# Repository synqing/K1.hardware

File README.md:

# K1.hardware

Agent-driven KiCad and PCB automation for K1-Lightwave hardware.

This repository contains public tooling, MCP servers, reference material, and prototype automation used around the K1-Lightwave hardware workflow. Product PCB files, fabrication outputs, BOMs, and private design documents are not published in the public HEAD of this repository.

> [!NOTE]
> This public surface is being cleaned up for transfer into the SpectraSynq organisation. Some legacy prototype tooling is preserved for reference, but it should not be treated as a stable package API until it is extracted into a dedicated tool repository.

## Quickstart

```bash
git clone https://github.com/synqing/K1.hardware.git
cd K1.hardware
python3 mcp/verify-servers.py
python3 mcp/test_rag.py
```

For Claude Code MCP setup, run:

```bash
python3 mcp/configure_claude.py
```

Some integrations need your own API credentials. See [SETUP_CREDENTIALS.md](docs/internal/legacy-root/SETUP_CREDENTIALS.md) for provider setup notes.

## What is here

- **MCP servers** in [mcp/](mcp/) for KiCad CLI automation, KiKit, KiBot, SKiDL, FreeRouting, component sourcing, fab operations, and local RAG.
- **Agent modules** in [agent/](agent/) for DFM checks, KiCad helpers, routing, impedance, thermal modelling, and orchestration.
- **Tool prototypes** in [tools/](tools/), including the KiCad footprint hunter and the preserved Elite PCB Designer prototype.
- **Reference docs** in [docs/](docs/) for public tooling notes, vendor references, datasheets, and legacy implementation notes.

## Repository layout

```text
K1.hardware/
|-- agent/                         Python modules for PCB automation workflows
|-- docs/                          Public references and legacy notes
|-- mcp/                           MCP servers used by agent-driven EDA workflows
|-- plugins/                       KiCad plugin experiments
|-- tools/
|   |-- elite-pcb-designer/        Prototype routing, placement, and validation tooling
|   `-- kicad-footprint-hunter/    Footprint discovery and board update utilities
|-- .github/                       Workflow definitions retained for review
|-- .gitignore
|-- LICENSE
`-- README.md
```

## Working with the tools

Use [mcp/verify-servers.py](mcp/verify-servers.py) to check local dependencies and MCP server availability. Use [mcp/test_rag.py](mcp/test_rag.py) to confirm the local RAG index can answer tooling queries.

The legacy Elite PCB Designer prototype now lives under [tools/elite-pcb-designer/legacy-pipeline/](tools/elite-pcb-designer/legacy-pipeline/). Run those scripts from that directory, and expect to provide your own KiCad input files.

## Community and support

- [Issues](../../issues) for bugs, cleanup findings, and extraction candidates.
- [Discord](https://discord.gg/8y8rXegU8j) for SpectraSynq build discussion.

## Licence

Code is licensed under Apache-2.0; see [LICENSE](LICENSE). Documentation is licensed under [CC BY 4.0](https://creativecommons.org/licenses/by/4.0/) unless a source document states otherwise.

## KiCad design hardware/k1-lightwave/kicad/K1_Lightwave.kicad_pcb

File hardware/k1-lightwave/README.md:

# K1 Lightwave Hardware Design — Tooling Guide

This folder contains the KiCad schematic, PCB layout, and supporting design files for the K1 Lightwave dual-ESP32-S3 music visualizer.

---

## Folder Structure

```
k1-lightwave/
├── kicad/
│   ├── K1_Lightwave.kicad_sch      ← Master schematic
│   ├── K1_Lightwave.kicad_pcb      ← PCB layout
│   ├── K1_Lightwave.kicad_pro      ← KiCad project file
│   ├── symbols/                    ← Custom/library symbols
│   ├── footprints/                 ← Custom/library footprints
│   └── 3d_models/                  ← 3D STEP/VRML models
├── skidl/
│   └── hello_board.py              ← Example SKiDL schematic generator
└── README.md                         ← You are here
```

---

## MCP Tool Commands

All tools are wired as Claude Code MCP servers. Use them to validate design changes.

### **Electrical Rules Check (ERC)**

```
sch_erc(schematic, out="erc.json", format="json", exit_code_violations=True)
```

**Example:**
```python
result = sch_erc("hardware/k1-lightwave/kicad/K1_Lightwave.kicad_sch", out="erc.json")
# Returns: {"returncode": 0, "ok": true, "summary": {"errors": 0, "warnings": 0}}
```

**Pass criteria:** `error_count == 0`

---

### **Design Rules Check (DRC)**

```
pcb_drc(board, out="drc.json", format="json", exit_code_violations=True)
```

**Example:**
```python
result = pcb_drc("hardware/k1-lightwave/kicad/K1_Lightwave.kicad_pcb", out="drc.json")
# Returns: {"returncode": 0, "ok": true, "summary": {"violations": 0}}
```

**Pass criteria:** `violations == 0` (JLC 4-layer rules in `design_rules.kicad_dru`)

---

### **Bill of Materials (BOM) Export**

```
sch_export_bom(schematic, out_csv="bom.csv", fields="*")
```

**Example:**
```python
result = sch_export_bom("hardware/k1-lightwave/kicad/K1_Lightwave.kicad_sch", out_csv="bom.csv")
# Exports: bom.csv with all component fields
```

---

### **Netlist Export** (for routing/SKiDL)

```
sch_export_netlist(schematic, out_net="project.net", fmt="kicadsexpr")
```

**Example:**
```python
result = sch_export_netlist("hardware/k1-lightwave/kicad/K1_Lightwave.kicad_sch", out_net="k1.net")
# Exports: S-expression netlist for DSN → routing workflow
```

---

### **Gerber/Drill/STEP/IPC-2581 Exports**

```
pcb_export_gerbers(board, out_dir="fab/gerbers")
pcb_export_drill(board, out_dir="fab/drill")
pcb_export_step(board, out_file="mechanical/board.step")
pcb_export_ipc2581(board, out_file="fab/board.ipc")
```

**Example:**
```python
pcb_export_gerbers("hardware/k1-lightwave/kicad/K1_Lightwave.kicad_pcb", out_dir="fab/gerbers")
pcb_export_drill("hardware/k1-lightwave/kicad/K1_Lightwave.kicad_pcb", out_dir="fab/drill")
pcb_export_step("hardware/k1-lightwave/kicad/K1_Lightwave.kicad_pcb", out_file="fab/board.step")
# Creates fab-ready artifacts
```

---

### **Netlist Generation from SKiDL**

```
skidl_gen_netlist(script_path="skidl/hello_board.py", out_net="skidl_out.net")
```

**Example:**
```python
result = skidl_gen_netlist("hardware/k1-lightwave/skidl/hello_board.py", out_net="k1.net")
# Returns: {"parts": 12, "nets": 8, "output": "/path/to/k1.net"}
```

---

### **Component Lookup (Nexar/LCSC)**

```
parts_search(q="ESP32-S3-WROOM-1", limit=3)
best_datasheet_url(mpn="WS2812B")
lcsc_search(keyword="C2653")
```

**Example:**
```python
result = parts_search("ESP32-S3-WROOM-1", limit=3)
# Returns: MPN, manufacturer, best_datasheet URL

ds = best_datasheet_url("WS2812B")
# Returns: {"mpn": "WS2812B", "url": "https://...", "ok": true}

item = lcsc_search("C2653")
# Returns: LCSC product info (pricing, stock, etc.)
```

---

### **Panelization (KiKit)**

```
kikit_panelize_grid(input_pcb, output_pcb, rows=4, cols=8, space_mm="2mm", tabs="full", cuts="vcuts; clearance: 0.4mm", rails_mm="5mm")
```

**Example:**
```python
result = kikit_panelize_grid(
    "hardware/k1-lightwave/kicad/K1_Lightwave.kicad_pcb",
    "hardware/k1-lightwave/kicad/K1_Lightwave_PANEL_4x8.kicad_pcb",
    rows=4, cols=8, space_mm="2mm", rails_mm="5mm"
)
# Creates panelized board with V-cuts and mousebites
```

---

### **JLC Assembly Pack (KiKit)**

```
kikit_fab_jlcpcb(board_or_panel, out_dir="fab/jlc", assembly=True, schematic="...", field="LCSC", autoname=True)
```

**Example:**
```python
result = kikit_fab_jlcpcb(
    "hardware/k1-lightwave/kicad/K1_Lightwave.kicad_pcb",
    out_dir="fab/jlc",
    assembly=True,
    schematic="hardware/k1-lightwave/kicad/K1_Lightwave.kicad_sch",
    field="LCSC"
)
# Generates: gerbers.zip, bom.csv, pos.csv (JLC-ready)
```

---

### **Interactive BOM (iBOM)**

```
generate(board_kicad_pcb, out_dir="docs/ibom", name_format="ibom", extra_fields="LCSC,MPN,Manufacturer")
```

**Example:**
```python
result = generate("hardware/k1-lightwave/kicad/K1_Lightwave.kicad_pcb", out_dir="docs/ibom")
# Creates: docs/ibom/ibom.html (self-contained assembly guide)
```

---

### **CI Automation (KiBot)**

```
kibot_run(project_dir="hardware/k1-lightwave", config_yaml="kibot.yaml", out_dir="_artifacts", schematic="...", board="...")
```

**Example:**
```python
result = kibot_run(
    project_dir="hardware/k1-lightwave",
    config_yaml="kibot.yaml",
    out_dir="_artifacts",
    schematic="kicad/K1_Lightwave.kicad_sch",
    board="kicad/K1_Lightwave.kicad_pcb"
)
# Runs full KiBot pipeline (ERC, DRC, exports, docs)
```

---

### **Autorouting (FreeRouting)**

```
route(dsn="export.dsn", ses_out="routed.ses", ignore_nets="", timeout_sec=300)
```

**Example:**
```python
result = route("kicad/K1_Lightwave.dsn", ses_out="kicad/K1_Lightwave.ses")
# Routes board from KiCad DSN export → SES session file
```

---

## ⚠️ Critical Safety: Dual 5V Rails

> **External LED 5V required.** USB-C 5V powers the controller only. Do not power LED strips from USB-C.
> Use the **LED_5V_IN** connector, one polyfuse per LED output, and keep LED return paths short.
>
> **Power-domain guard enabled:** Schematic-level check prevents shorts between `VBUS_USB_5V` and `LED_5V` nets.
> If any component accidentally ties both nets, the fab pipeline will reject the design.

---

## Design Rules & Constraints

### **Manufacturing (JLC PCBWay 4-layer)**

- **Minimum trace width:** 0.1mm
- **Minimum clearance:** 0.1mm
- **Via diameter (finished):** 0.3mm min
- **Stackup:** Signal / Plane / Plane / Signal
- **Impedance (controlled):** 50Ω differential for high-speed signals

### **Electrical (K1 Lightwave)**

- **VCC (3.3V logic):** ±0.1V regulation
- **Power (5V input):** 5A budget, adjust per LED load
- **USB 5V (controller):** Powers MCUs + audio codec only via LDO
- **LED 5V (external):** Separate connector; never tied to USB rail
- **I2S audio:** BCLK/LRCLK/SD differential, <0.5mm lengths matched
- **SPI (LED data):** <5mm tracklength to level shifter + MCU
- **Ground:** Multi-point return (polygon fill on both internal planes)

### **Thermal**

- **LED driver max dissipation:** 1.5W (estimate via chain coverage)
- **MCU under full load:** Monitor thermal rise via STEP export
- **Thermal vias under high-current:** 8–16× 0.3mm vias per component

### **Layout Best Practices**

- **RF keepout:** 5mm from ESP32 module antenna edge
- **Audio coupling:** Ground guard on I2S traces; min 0.5mm clearance from LED switching
- **Power distribution:** Use star grounding; separate analog/digital returns only if needed
- **Test points:** Add TP for each major rail + UART + LED data/clock

---

## Validation Checklist

Before committing design changes, run:

```bash
# 1. ERC
sch_erc("kicad/K1_Lightwave.kicad_sch", out="erc.json")
# Expected: error_count == 0

# 2. DRC
pcb_drc("kicad/K1_Lightwave.kicad_pcb", out="drc.json")
# Expected: violations == 0

# 3. BOM & component availability
sch_export_bom("kicad/K1_Lightwave.kicad_sch", out_csv="bom.csv")
parts_search("ESP32-S3-WROOM-1", limit=3)  # verify stock
best_datasheet_url("SPH0645")  # verify datasheets available

# 4. Mechanical (3D check)
pcb_export_step("kicad/K1_Lightwave.kicad_pcb", out_file="fab/board.step")
# View in 3D viewer to catch clearance issues

# 5. Manufacturing data
pcb_export_ipc2581("kicad/K1_Lightwave.kicad_pcb", out_file="fab/board.ipc")
# For DFM analysis at fab
```

---

## Documentation

- **Hardware PRD:** `/docs/prd/02-hardware-prd.md`
- **Validation Plan:** `/docs/prd/03-validation-plan.md`
- **Datasheets:** `/docs/datasheets/` (ESP32-S3, SPH0645, IM69D130, WS2812B, SN74AHCT125, etc.)
- **Governance:** `/claude/GOVERNANCE.md` (design change protocol)

---

## References

- **KiCad CLI:** https://docs.kicad.org/cli/
- **KiCad Project:** K1_Lightwave.kicad_pro (PCBNew, Schematic Editor)
- **JLC/PCBWay DRC:** `/docs/datasheets/jlc-pcbway-4layer-drc.pdf`
- **ESP32-S3 Datasheet:** `/docs/datasheets/esp32-s3_datasheet_en.pdf`

---

**Last updated:** Oct 23, 2025
**Status:** Project scaffold — ready for design work

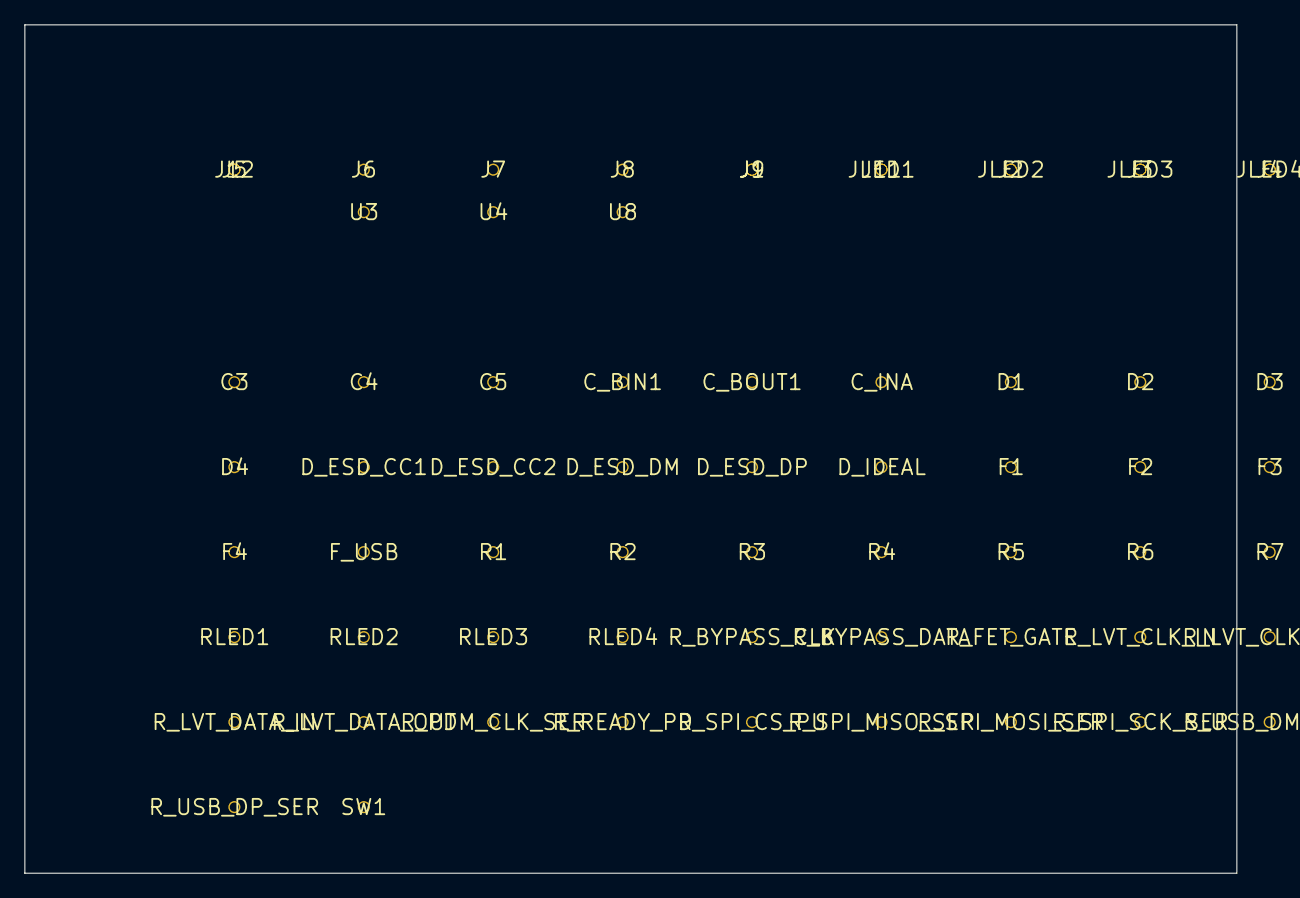
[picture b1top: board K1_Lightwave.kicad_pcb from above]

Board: 4 copper layers, 100.0 x 70.0 mm, 65 parts (0 on the bottom side), 12 nets, no tracks yet.

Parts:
C3: 1u
C4, C5: 12p
C_BIN1: 10u
C_BOUT1: 10u
C_INA: 100n
D1, D2, D3, D4: TVS5V
D_ESD_CC1, D_ESD_CC2: SMF05CA
D_ESD_DM: SMAJ5.0A
D_ESD_DP: SMAJ5.0A
D_IDEAL: Schottky
F1, F2, F3, F4: Polyfuse_0.75A
F_USB: 1A_1206
J1: USB_C_Receptacle_USB2.0_14P
J2: LED_5V_IN
J3: I2C_PORT_1_3V3
J4: I2C_PORT_2_3V3
J5: I2C_PORT_3_5V
J6: I2C_PORT_4_5V
J7: I2S_MIC_1
J8: I2S_MIC_2
J9: PDM_MIC_HEADER
J11: K1-M2B_COM-A
J12: ESP32-S3_COM-B_LOGICAL
JLED1: LED_OUT_1
JLED2: LED_OUT_2
JLED3: LED_OUT_3
JLED4: LED_OUT_4
R1, R2: 5.1k
R3, R4, R5, R6: 10k
R7: 0.05R
RLED1, RLED2, RLED3, RLED4: 330R
R_BYPASS_CLK: 0R
R_BYPASS_DATA: 0R
R_FET_GATE: 10k
R_LVT_CLK_IN: 0R
R_LVT_CLK_OUT: 0R
R_LVT_DATA_IN: 0R
R_LVT_DATA_OUT: 0R
R_PDM_CLK_SER: 33R
R_READY_PD: 100k
R_SPI_CS_PU: 10k
R_SPI_MISO_SER: 33R
R_SPI_MOSI_SER: 33R
R_SPI_SCK_SER: 33R
R_USB_DM_SER: 27R
R_USB_DP_SER: 27R
SW1: Push_Button
U3: Logic_Shifter_74AHCT125
U4: 24LC256
U8: Logic_Buffer_SN74AXC2T245

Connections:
+3V3: C_BOUT1.1, C_INA.1, J7.1, J8.1, J9.1, J11.1, J12.1, R3.1, R4.1, R5.1, R6.1, R_FET_GATE.1, R_SPI_CS_PU.1
COMA_PDM_CLK: R_BYPASS_CLK.1, R_LVT_CLK_IN.1, R_PDM_CLK_SER.1
GND: J3.1, J4.1, J5.1, J6.1
LED_5V: F1.1, F2.1, F3.1, F4.1, R7.1
LED_5V_RAW: D_IDEAL.1, J2.1
MIC_PDM_DATA: R_BYPASS_DATA.1, R_LVT_DATA_IN.1
unnamed: D_ESD_CC1.1, R1.1
unnamed: D_ESD_CC2.1, R2.1
unnamed: D1.1, JLED1.1
unnamed: D2.1, JLED2.1
unnamed: D3.1, JLED3.1
unnamed: D4.1, JLED4.1

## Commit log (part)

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2025-10-23 Enable manual workflow trigger for on-demand fab artifact generation
2025-10-23 Fix CI: Install KiCad on Ubuntu runner for KiBot to work
2025-10-23 Fix: Install KiCad from apt, KiBot from pipx (correct package sources)
2025-10-23 Fix: Apply four critical design corrections to SKiDL netlist
    - CRITICAL: Replace TPS62133 (BOOST) with TPS62160 (BUCK) for 5V→3.3V conversion
    * TPS62133 was step-UP converter; board would not power 3.3V logic
    * TPS62160 is proper step-DOWN synchronous converter (5V→3.3V, 1.5A)
    - CRITICAL: Fix ideal diode topology - replace Si2301 (N-ch) with BSS84 (P-ch)
    * Si2301 is N-channel; cannot properly block reverse current in OR-ing circuit
    * BSS84 P-channel provides proper gate drive for LTC4412 reverse-blocking
2025-10-23 Fix: Remove error suppression from KiBot step to show actual failures
2025-10-23 CI: Add SKiDL netlist generation step before KiBot fab artifact generation
2025-10-23 Fix: Make SKiDL cross-platform with proper KiCad library path detection
2025-10-23 Fix: Set correct KICAD9/8/7_SYMBOL_DIR environment variables for SKiDL
2025-10-23 Docs: Add comprehensive manufacturing package and design validation summary
2025-10-23 Fix: Add comprehensive KiCad symbol directory environment variables for all SKiDL lib versions
2025-10-23 CRITICAL FIX: Set KiCad library paths in Python BEFORE SKiDL import
2025-10-23 SUCCESS: Generated complete K1 Lightwave netlist from SKiDL (64KB, all components and nets)
2025-10-23 CI: Simplify workflow - use committed netlist, skip SKiDL generation, run KiBot only
2025-10-24 fix: Update board generation to use actual footprint names and proper tab indentation
2025-10-24 docs: Add board population guide with proper plugin workflow
    - Documented the solution: use K1_ContractedPlace_PRO plugin (runs in KiCad GUI)
    - Explained why CLI/programmatic approaches fail: no library context
    - Provided step-by-step workflow from skeleton to manufacturing exports
    - Installed K1_ContractedPlace_PRO plugin to KiCad scripting directory
    - Board skeleton verified as valid and ready for GUI-based population
2025-10-24 config: Fix board stackup (2→4 layer), outline (60→70mm), and add layer definitions
    CRITICAL FIXES for end-to-end pipeline:
    1. **Stackup**: Added In1.Cu and In2.Cu layers with FR4 dielectric
    - Now: 4-layer board (F.Cu, In1.Cu, In2.Cu, B.Cu) with proper stackup
    - Total thickness: 0.6mm (0.035mm Cu × 4 + 0.17mm FR4 × 3)
    2. **Board Outline**: Fixed from 100×60mm to 100×70mm per contract
    - Origin: (0, 0) instead of offset (10, 10)
2025-10-24 docs: Add pipeline readiness checklist - all blockers resolved
    ✅ READY FOR END-TO-END EXECUTION
    Blockers fixed:
    1. Board stackup: 2-layer → 4-layer (F.Cu, In1.Cu, In2.Cu, B.Cu with FR4 dielectric)
    2. Board outline: 100×60mm → 100×70mm, origin at (0,0)
    3. FreeRouting JAR: Confirmed present at tools/freerouting.jar (64MB)
    Pipeline components verified:
2025-10-24 feat: Complete K1 PCB pipeline configuration - all blockers resolved
    ## Summary
    Comprehensive end-to-end K1 PCB design pipeline is now fully configured and ready
    for clean execution. All three critical blockers identified and fixed.
    ## Critical Fixes Implemented
    ### 1. Board Stackup Configuration (2→4 Layer)
    - **Added**: In1.Cu and In2.Cu internal copper layers
2025-11-10 feat: Add comprehensive documentation to all modules
    This commit adds comprehensive docstrings to all Python modules in the repository, following Google-style conventions. It also updates the main README.md with a detailed developer guide.
    Key changes:
    - Added docstrings to all public functions, methods, and classes in the core modules and the `agent/` directory.
    - Updated the main `README.md` to include a "Developer Guide" section covering the project's purpose, setup, and usage.
    - Documented all test files to clarify their purpose.
2025-11-10 feat: Add deployment guide
    Adds a `DEPLOYMENT_GUIDE.md` file with instructions on how to set up the required KiCad environment to run the PCB design automation tool. This guide addresses the feedback from the code review and p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
2025-11-11 docs: Add comprehensive deployment validation report
    This report provides a complete review of the K1 Hardware PCB design
    automation pipeline, including:
    - Architecture validation (7-phase orchestrator)
    - MCP server implementation review (10 servers)
    - KiCad plugin analysis (4 plugins)
    - Design contract system evaluation
2025-11-11 chore: Add .gitignore for Python and KiCad artifacts
    Ignore common temporary files:
    - Python cache files (__pycache__, *.pyc)
    - Virtual environments
    - KiCad backup files (*-bak, *-save)
    - Build output directories (fabpack_out/, k1_design_output*)
    - Log files and temporary artifacts
